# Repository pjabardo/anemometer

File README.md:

# envconds
Temperature, Pressure and Humidity measurement board and software

The objective of this project is to develop a board that reads environmental conditions including
 * Temperature using DS18B20 sensor
 * Pressure using the BMP280 sensor
 * Humidity using the DHT22 sensor

In the future, more sensors could be added.

The board uses a ESP32 microcontroller, in particular the Devkit v1 board with 30 pins. Embeded programming is done using arduino framework.

The folder `kicad` contains the schematics of the board.

For now a simple communication protocol over the serial line is used. In the future MQTT should be used.

To read a value, user should send the command `*XY` where `X` refers to the sensor and `Y` the variable being read. The following variables can be read:

 * `HH` - Humidity from the DHT22
 * `HT` - Temperature from the DHT22
 * `PP` - Atmospheric pressure from the BMP280
 * `PT` - Temperature from the BMP280
 * `Tx' - where x is the temperature sensor.

 To read the atmospheric pressure, the command `*PP` should be sent to the microcontroller. The response is sent as a line of text containing the value as an ASCII string.

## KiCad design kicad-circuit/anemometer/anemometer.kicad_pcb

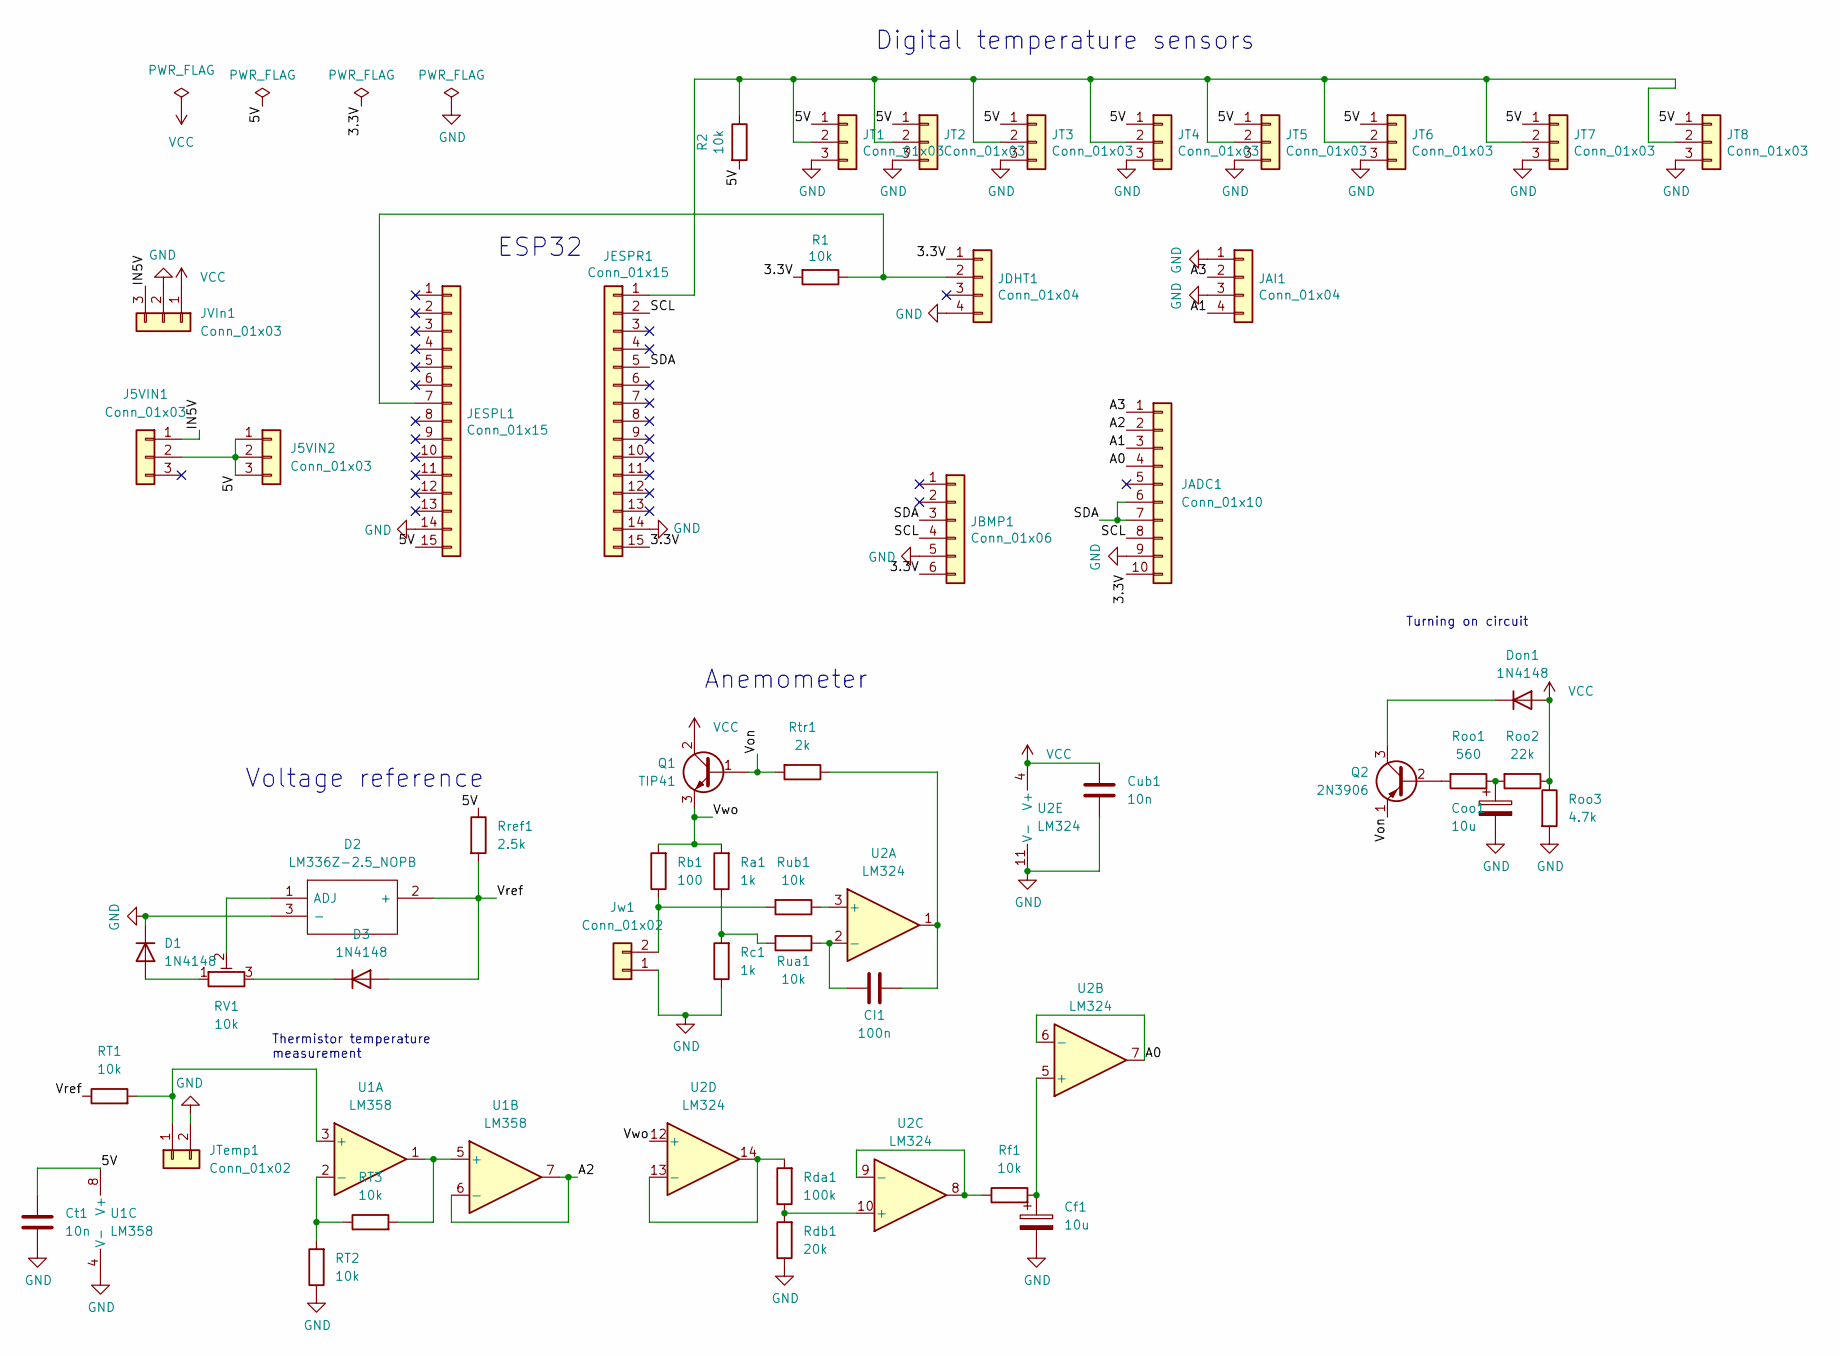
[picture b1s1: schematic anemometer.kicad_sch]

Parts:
CI1: 100n; C_Rect_L7.2mm_W3.5mm_P5.00mm_FKS2_FKP2_MKS2_MKP2
Cf1: 10u; CP_Radial_D5.0mm_P2.50mm
Coo1: 10u; CP_Radial_D5.0mm_P2.50mm
Ct1: 10n; C_Disc_D5.0mm_W2.5mm_P2.50mm
Cub1: 10n; C_Disc_D5.0mm_W2.5mm_P2.50mm
D1, D3: 1N4148; D_DO-35_SOD27_P7.62mm_Horizontal
D2: LM336Z-2.5_NOPB; TO-92_Inline_Wide; Manufacturer_Part_Number LM336Z-2.5/NOPB; Mouser Part Number 926-LM336Z-2.5/NOPB
Don1: 1N4148; D_DO-35_SOD27_P7.62mm_Horizontal
J5VIN1, J5VIN2: Conn_01x03; PinSocket_1x03_P2.54mm_Vertical
JADC1: Conn_01x10; PinSocket_1x10_P2.54mm_Vertical
JAI1: Conn_01x04; TerminalBlock_bornier-4_P5.08mm
JBMP1: Conn_01x06; PinSocket_1x06_P2.54mm_Vertical
JDHT1: Conn_01x04; PinSocket_1x04_P2.54mm_Vertical
JESPL1: Conn_01x15; PinSocket_1x15_P2.54mm_Vertical
JESPR1: Conn_01x15; PinSocket_1x15_P2.54mm_Vertical
JT1, JT2, JT3, JT4, JT5, JT6, JT7, JT8: Conn_01x03; PinHeader_1x03_P2.54mm_Vertical
JTemp1: Conn_01x02; TerminalBlock_bornier-2_P5.08mm
JVIn1: Conn_01x03; TerminalBlock_bornier-3_P5.08mm
Jw1: Conn_01x02; TerminalBlock_bornier-2_P5.08mm
Q1: TIP41; TO-220-3_Horizontal_TabUp
Q2: 2N3906; TO-92_Inline_Wide
R1, R2: 10k; R_Axial_DIN0207_L6.3mm_D2.5mm_P10.16mm_Horizontal
RT1, RT2, RT3: 10k; R_Axial_DIN0207_L6.3mm_D2.5mm_P10.16mm_Horizontal
RV1: 10k; Potentiometer_Bourns_3296W_Vertical
Ra1: 1k; R_Axial_DIN0207_L6.3mm_D2.5mm_P10.16mm_Horizontal
Rb1: 100; R_Axial_DIN0414_L11.9mm_D4.5mm_P15.24mm_Horizontal
Rc1: 1k; R_Axial_DIN0207_L6.3mm_D2.5mm_P10.16mm_Horizontal
Rda1: 100k; R_Axial_DIN0207_L6.3mm_D2.5mm_P10.16mm_Horizontal
Rdb1: 20k; R_Axial_DIN0207_L6.3mm_D2.5mm_P10.16mm_Horizontal
Rf1: 10k; R_Axial_DIN0207_L6.3mm_D2.5mm_P10.16mm_Horizontal
Roo1: 560; R_Axial_DIN0207_L6.3mm_D2.5mm_P10.16mm_Horizontal
Roo2: 22k; R_Axial_DIN0207_L6.3mm_D2.5mm_P10.16mm_Horizontal
Roo3: 4.7k; R_Axial_DIN0207_L6.3mm_D2.5mm_P10.16mm_Horizontal
Rref1: 2.5k; R_Axial_DIN0207_L6.3mm_D2.5mm_P10.16mm_Horizontal
Rtr1: 2k; R_Axial_DIN0207_L6.3mm_D2.5mm_P10.16mm_Horizontal
Rua1: 10k; R_Axial_DIN0207_L6.3mm_D2.5mm_P10.16mm_Horizontal
Rub1: 10k; R_Axial_DIN0207_L6.3mm_D2.5mm_P10.16mm_Horizontal
U1: LM358; DIP-8_W7.62mm_LongPads
U2: LM324; DIP-14_W7.62mm_Socket_LongPads

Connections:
/3.3V: JADC1.10, JBMP1.6, JDHT1.1, JESPR1.15, R1.2
/5V: Ct1.1, J5VIN1.2, J5VIN2.1, J5VIN2.2, J5VIN2.3, JESPL1.15, JT1.1, JT2.1, JT3.1, JT4.1, JT5.1, JT6.1, JT7.1, JT8.1, R2.2, Rref1.1, U1.8 (V+)
/A0: JADC1.4, U2.6 (-), U2.7
/A1: JADC1.3, JAI1.4
/A2: JADC1.2, U1.6 (-), U1.7
/A3: JADC1.1, JAI1.2
/IN5V: J5VIN1.1, JVIn1.3
/SCL: JADC1.8, JBMP1.4, JESPR1.2
/SDA: JADC1.6, JADC1.7, JBMP1.3, JESPR1.5
/Von: Q1.1 (B), Q2.1 (E), Rtr1.2
/Vref: D2.2 (+), D3.2 (A), RT1.1, Rref1.2
/Vwo: Q1.3 (E), Ra1.2, Rb1.2, U2.12 (+)
GND: Cf1.2, Coo1.2, Ct1.2, Cub1.2, D1.1 (K), D2.3 (-), JADC1.9, JAI1.1, JAI1.3, JBMP1.5, JDHT1.4, JESPL1.14, JESPR1.14, JT1.3, JT2.3, JT3.3, JT4.3, JT5.3, JT6.3, JT7.3, JT8.3, JTemp1.2, JVIn1.2, Jw1.1, RT2.1, Rc1.1, Rdb1.1, Roo3.2, U1.4 (V-), U2.11 (V-)
unnamed: CI1.1, Rua1.1, U2.2 (-)
unnamed: CI1.2, Rtr1.1, U2.1
unnamed: Cf1.1, Rf1.2, U2.5 (+)
unnamed: Coo1.1, Roo1.1, Roo2.2
unnamed: D1.2 (A), RV1.1
unnamed: D2.1 (ADJ), RV1.2
unnamed: D3.1 (K), RV1.3
unnamed: Don1.1 (K), Q2.3 (C)
unnamed: JDHT1.2, JESPL1.7, R1.1
unnamed: JESPR1.1, JT1.2, JT2.2, JT3.2, JT4.2, JT5.2, JT6.2, JT7.2, JT8.2, R2.1
unnamed: JTemp1.1, RT1.2, U1.3 (+)
unnamed: Jw1.2, Rb1.1, Rub1.2
unnamed: Q2.2 (B), Roo1.2
unnamed: RT2.2, RT3.1, U1.2 (-)
unnamed: RT3.2, U1.1, U1.5 (+)
unnamed: Ra1.1, Rc1.2, Rua1.2
unnamed: Rda1.1, Rdb1.2, U2.10 (+)
unnamed: Rda1.2, U2.13 (-), U2.14
unnamed: Rf1.1, U2.8, U2.9 (-)
unnamed: Rub1.1, U2.3 (+)
VCC: Cub1.1, Don1.2 (A), JVIn1.1, Q1.2 (C), Roo2.1, Roo3.1, U2.4 (V+)

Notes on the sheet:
ESP32
Thermistor temperature measurement
Digital temperature sensors
Turning on circuit
Anemometer
Voltage reference

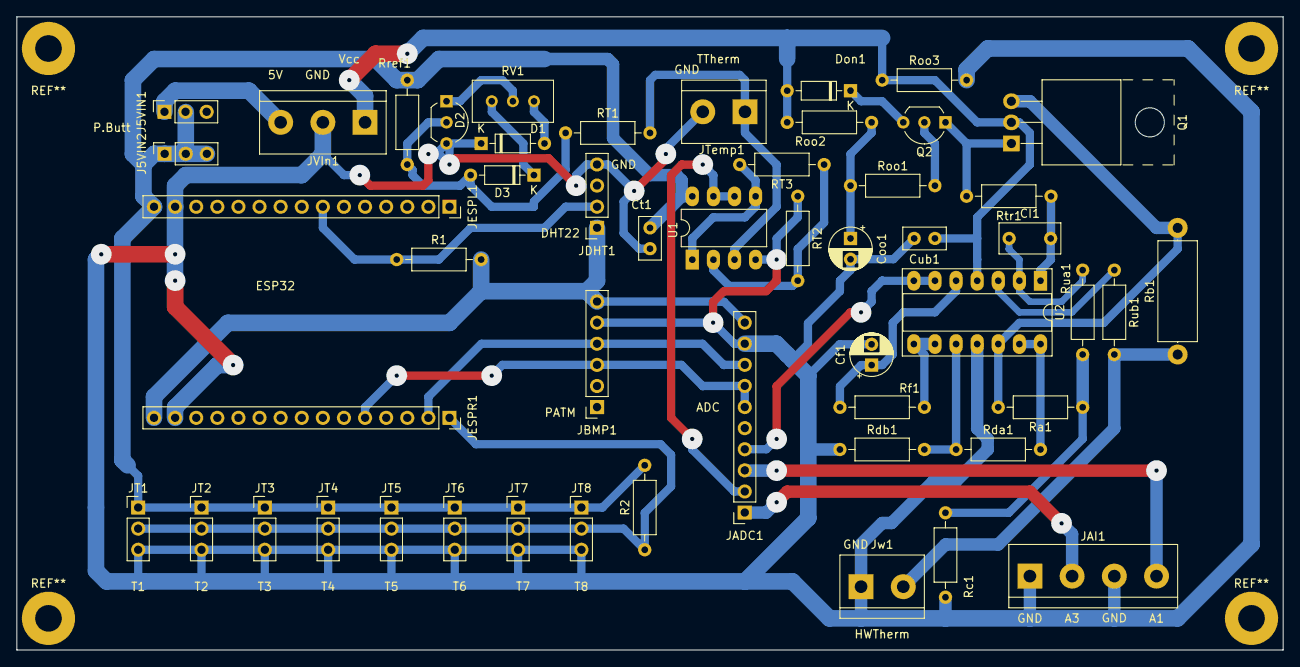
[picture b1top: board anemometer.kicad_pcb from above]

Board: 2 copper layers, 152.4 x 76.2 mm, 51 parts (0 on the bottom side), 34 nets.

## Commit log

2022-11-03 Adding KiCAD files to the repository
    I believe the circuit is correct. I will need to check the circuit thoroughly and then build the board.
2022-11-04 Changed a little bit the tracks on the upper side
    Since I will be building the boards by hand, the upper side tracks should no pass under resistors and other components so I rearranged a few things.
2022-11-14 Implemented basic arduino code and python code
    It appears to be working. But I still need improve the software, basically a need to implement some sort of streaming from the analog to digital converter.
    I found an error on the board: the temperature circuit was wrong. I corrected it on the physical board I built but I still need to correct the Kicad project.
    Another thing that I should improve is the disposition of the digital temperature sensors. If I just switch pins I could solder a digital sensor directly on the board. May be I will doit later...
2022-11-17 Corrected the thermistor temperature circuit.
    There was a mistake. I corrected it ion the board that I built and now it is corrected in the Kicad circuit.
2022-11-17 Switched pins of DS18B20 temp. sensor
    Now the tracks are positioned in the same orientation as the pins in the TO-92 packaging. Not important but now I can solder one sensor directly on the board.
2022-11-18 Moved some components so that the TIP41 transistor can lay on its back
2022-11-28 Using Bluetooth.
    Ugly but just a demo for now.
2023-02-01 Working on the software
    Not working yet. Just testing stuff
2023-03-20 Working on wifi
    COuldn't do anything besides connecting to the wifi router.
    Still figuring things out. This code is crap, just for experimenting.
2023-04-07 Working on the software
    Not much done but I'm figuring out the best structure.
2023-09-18 Improved software
    I think I'm working out a better archictecture.
2023-09-19 Improving the interface. Now we can get an individual reading using READ X
2023-09-27 Changing notation for private variables from var_ to _var
2023-10-03 Improved the software *a lot*
    Now we can choose which AI channels should be read and we can stop data acquisition in the middle of a scan!
    We can also set the temperature resolution but I couldn't notice any difference in speed. I will have to study this more.
    What I need to do now is improve flexibility in using the DS18b20 temperature sensors.
2023-10-05 Basic software interface developped.
    I still need to study the sampling rates better. But all appears to be working.
2023-10-05 Improving the reliability of the the code
    I have been experiencing problems with the power supply I believe. Nothing to do with this but still...
2023-10-17 Now the ESP32 can be used as an access point
    Just define the _ANEM_AP_
2023-10-20 Commented out the code to set the esp32 as an access point
2025-05-14 Circuit looks like it is working on KiCAD 9
2025-05-14 Moved things to PlatformIO and started to implement version with MQTT
    MQTT might be nice for a few things. I will still need to improve the
    interface but I will need study little bit the MQTT to make a nice
    interface.
2025-05-15 Removed the comm stuff.
    I will develop a new mqtt interface that is flexible.
2025-05-18 Working on it. Some serious bug. Nothing is working
    I will have to figure out what is going on.
2025-05-19 Full interface appears to be working
    Now we can add or remove stuff that should be acquired and published in the MQTT broker. I need to setup better defaults and test the interface.
2025-05-20 Deleted a few useless things.
    And did more extensive testing. I will try to keep this running for a few days to see what happens.
2025-05-22 Added a unit field to each measurement and AI output is now voltage.
    The code compiles but I still need test it with the board operating.
2025-05-23 Setting up defaults
    The temperature of the BMP280 is not read by default. The board inside the box warms up and the temperature is not very accurate.
    I have also disabled the analog input. There are several issues with the anemometer circuit. But the board is good enough for environment measurements.
2025-05-26 Setting up retained params is called in reconnect
    Now if the broker goes down, when reconnecting, the retained topics will be published again.
2025-05-28 Calibration correction for atmospheric pressure
    Also prepared for calibration of temperature sensors (DS18B20).
    I should think about a generic interface for calibration curves and units.
2025-07-24 Corrected bug when reading DS18B20 temperature sensors
    Only the first detected was being read.
